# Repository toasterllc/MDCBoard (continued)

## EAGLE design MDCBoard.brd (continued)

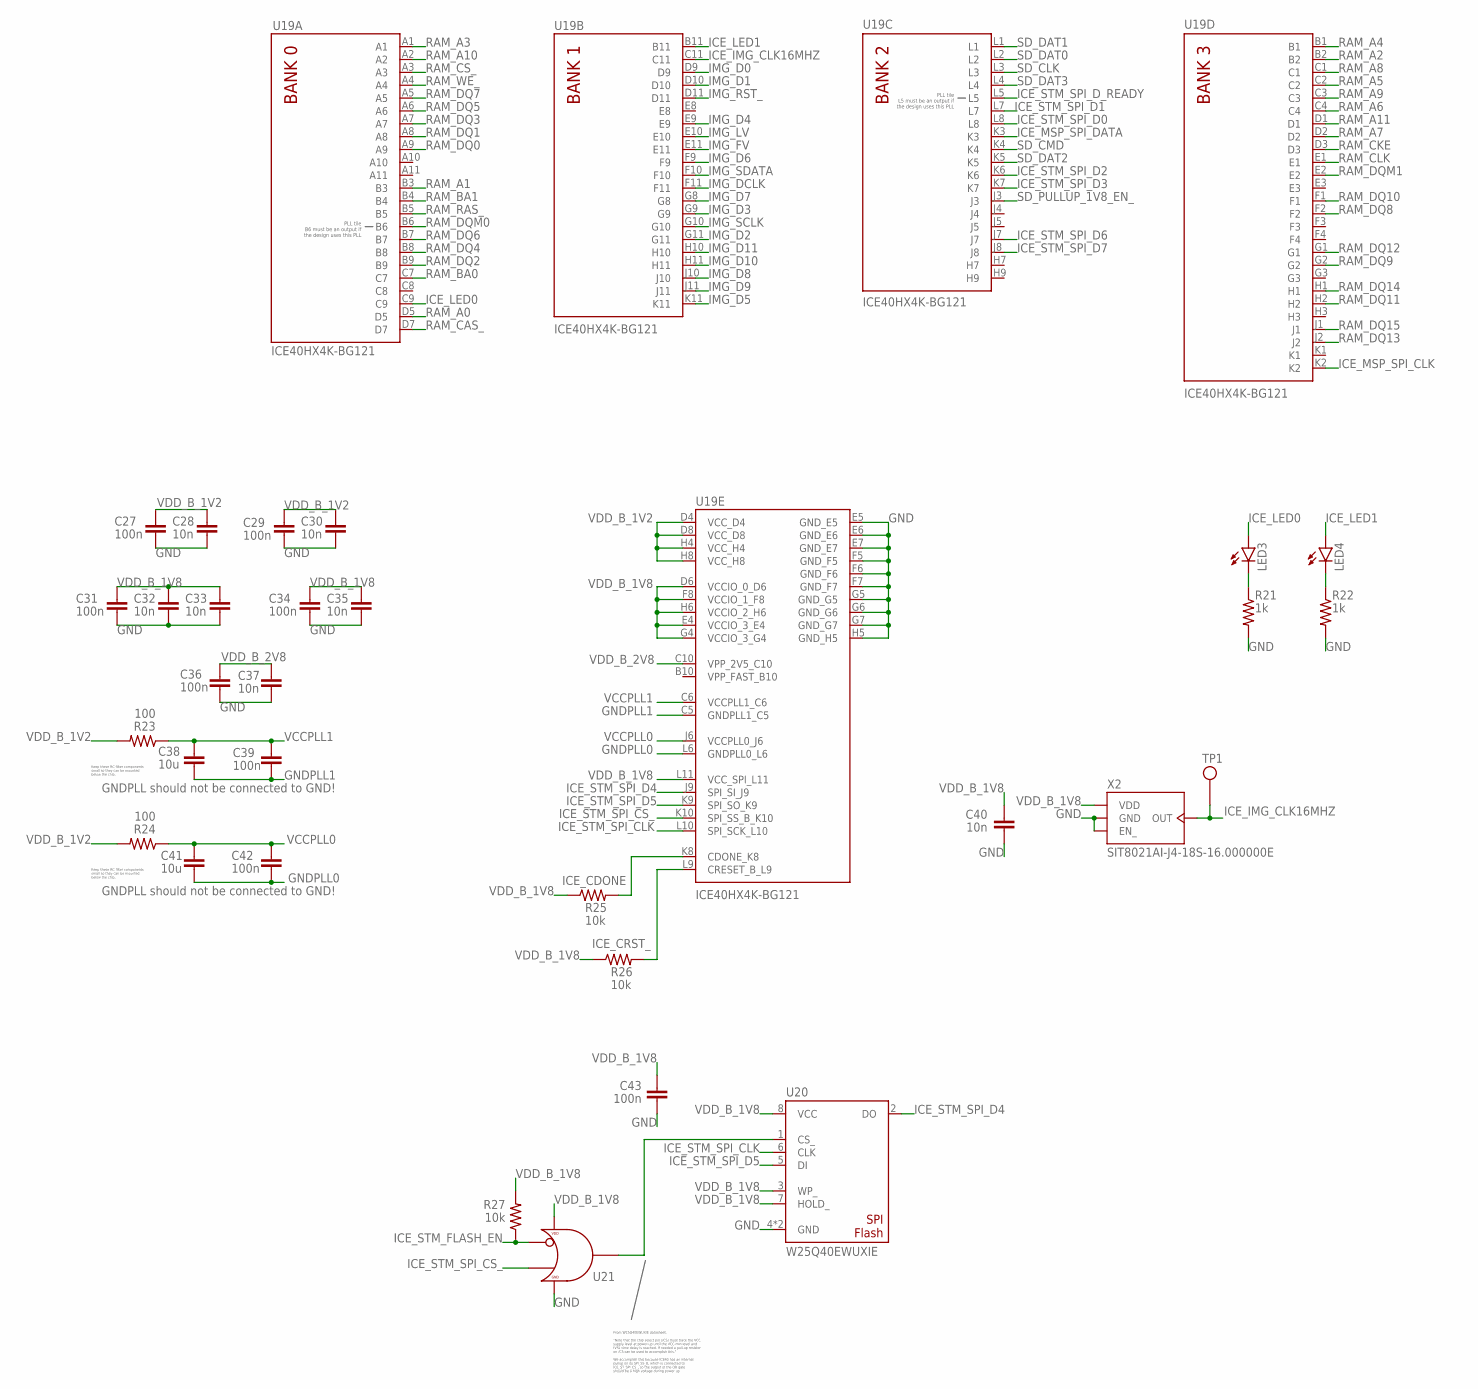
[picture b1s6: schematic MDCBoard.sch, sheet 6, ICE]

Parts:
C27, C29, C31, C34, C36, C39, C42, C43: 100n; 0402
C28, C30, C32, C33, C35, C37, C40: 10n; 0402
C38, C41: 10u; 0805
LED3, LED4: LEDLED-0603; LED-0603
R21, R22: 1k; 0402
R23, R24: 100; 0402
R25, R26, R27: 10k; 0402
TP1: TEST-POINT
U19: LATTICE-ICE40HX4K-BG121
U20: WINBOND-W25Q40EW; WINBOND-W25Q40EWUXIE
U21: NEXPERIA-74LVC1G98-OR-INV-INPUT; NEXPERIA-SOT363
X2: SITIME-SIT8021

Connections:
GND: C27.2, C28.2, C29.2, C30.2, C31.2, C32.2, C33.2, C34.2, C35.2, C36.2, C37.2, C40.2, C43.2, R21.2, R22.2, U19.E5 (GND_E5), U19.E6 (GND_E6), U19.E7 (GND_E7), U19.F5 (GND_F5), U19.F6 (GND_F6), U19.F7 (GND_F7), U19.G5 (GND_G5), U19.G6 (GND_G6), U19.G7 (GND_G7), U19.H5 (GND_H5), U20.4 (GND), U20.9 (GND), U21.2 (GND), U21.3 (GND), X2.1 (EN_), X2.4 (GND); also elsewhere on the board
GNDPLL0: C41.2, C42.2, U19.L6 (GNDPLL0_L6)
GNDPLL1: C38.2, C39.2, U19.C5 (GNDPLL1_C5)
ICE_CDONE: R25.2, U19.K8 (CDONE_K8); also elsewhere on the board
ICE_CRST_: R26.2, U19.L9 (CRESET_B_L9); also elsewhere on the board
ICE_IMG_CLK16MHZ: TP1.X, U19.C11, X2.2 (OUT); also elsewhere on the board
ICE_LED0: LED3.A, U19.C9
ICE_LED1: LED4.A, U19.B11
ICE_MSP_SPI_CLK: U19.K2; also elsewhere on the board
ICE_MSP_SPI_DATA: U19.K3; also elsewhere on the board
ICE_STM_FLASH_EN: R27.1, U21.1 (IN1); also elsewhere on the board
ICE_STM_SPI_CLK: U19.L10 (SPI_SCK_L10), U20.6 (CLK); also elsewhere on the board
ICE_STM_SPI_CS_: U19.K10 (SPI_SS_B_K10), U21.6 (IN2); also elsewhere on the board
ICE_STM_SPI_D0: U19.L8; also elsewhere on the board
ICE_STM_SPI_D1: U19.L7; also elsewhere on the board
ICE_STM_SPI_D2: U19.K6; also elsewhere on the board
ICE_STM_SPI_D3: U19.K7; also elsewhere on the board
ICE_STM_SPI_D4: U19.J9 (SPI_SI_J9), U20.2 (DO); also elsewhere on the board
ICE_STM_SPI_D5: U19.K9 (SPI_SO_K9), U20.5 (DI); also elsewhere on the board
ICE_STM_SPI_D6: U19.J7; also elsewhere on the board
ICE_STM_SPI_D7: U19.J8; also elsewhere on the board
ICE_STM_SPI_D_READY: U19.L5; also elsewhere on the board
IMG_D0: U19.D9; also elsewhere on the board
IMG_D1: U19.D10; also elsewhere on the board
IMG_D2: U19.G11; also elsewhere on the board
IMG_D3: U19.G9; also elsewhere on the board
IMG_D4: U19.E9; also elsewhere on the board
IMG_D5: U19.K11; also elsewhere on the board
IMG_D6: U19.F9; also elsewhere on the board
IMG_D7: U19.G8; also elsewhere on the board
IMG_D8: U19.J10; also elsewhere on the board
IMG_D9: U19.J11; also elsewhere on the board
IMG_D10: U19.H11; also elsewhere on the board
IMG_D11: U19.H10; also elsewhere on the board
IMG_DCLK: U19.F11; also elsewhere on the board
IMG_FV: U19.E11; also elsewhere on the board
IMG_LV: U19.E10; also elsewhere on the board
IMG_RST_: U19.D11; also elsewhere on the board
IMG_SCLK: U19.G10; also elsewhere on the board
IMG_SDATA: U19.F10; also elsewhere on the board
unnamed: LED3.C, R21.1
unnamed: LED4.C, R22.1
unnamed: U20.1 (CS_), U21.4 (OUT)
RAM_A0: U19.D5; also elsewhere on the board
RAM_A1: U19.B3; also elsewhere on the board
RAM_A2: U19.B2; also elsewhere on the board
RAM_A3: U19.A1; also elsewhere on the board
RAM_A4: U19.B1; also elsewhere on the board
RAM_A5: U19.C2; also elsewhere on the board
RAM_A6: U19.C4; also elsewhere on the board
RAM_A7: U19.D2; also elsewhere on the board
RAM_A8: U19.C1; also elsewhere on the board
RAM_A9: U19.C3; also elsewhere on the board
RAM_A10: U19.A2; also elsewhere on the board
RAM_A11: U19.D1; also elsewhere on the board
RAM_BA0: U19.C7; also elsewhere on the board
RAM_BA1: U19.B4; also elsewhere on the board
RAM_CAS_: U19.D7; also elsewhere on the board
RAM_CKE: U19.D3; also elsewhere on the board
RAM_CLK: U19.E1; also elsewhere on the board
RAM_CS_: U19.A3; also elsewhere on the board
RAM_DQ0: U19.A9; also elsewhere on the board
RAM_DQ1: U19.A8; also elsewhere on the board
RAM_DQ2: U19.B9; also elsewhere on the board
RAM_DQ3: U19.A7; also elsewhere on the board
RAM_DQ4: U19.B8; also elsewhere on the board
RAM_DQ5: U19.A6; also elsewhere on the board
RAM_DQ6: U19.B7; also elsewhere on the board
RAM_DQ7: U19.A5; also elsewhere on the board
RAM_DQ8: U19.F2; also elsewhere on the board
RAM_DQ9: U19.G2; also elsewhere on the board
RAM_DQ10: U19.F1; also elsewhere on the board
RAM_DQ11: U19.H2; also elsewhere on the board
RAM_DQ12: U19.G1; also elsewhere on the board
RAM_DQ13: U19.J2; also elsewhere on the board
RAM_DQ14: U19.H1; also elsewhere on the board
RAM_DQ15: U19.J1; also elsewhere on the board
RAM_DQM0: U19.B6; also elsewhere on the board
RAM_DQM1: U19.E2; also elsewhere on the board
RAM_RAS_: U19.B5; also elsewhere on the board
RAM_WE_: U19.A4; also elsewhere on the board
SD_CLK: U19.L3; also elsewhere on the board
SD_CMD: U19.K4; also elsewhere on the board
SD_DAT0: U19.L2; also elsewhere on the board
SD_DAT1: U19.L1; also elsewhere on the board
SD_DAT2: U19.K5; also elsewhere on the board
SD_DAT3: U19.L4; also elsewhere on the board
SD_PULLUP_1V8_EN_: U19.J3; also elsewhere on the board
VCCPLL0: C41.1, C42.1, R24.1, U19.J6 (VCCPLL0_J6)
VCCPLL1: C38.1, C39.1, R23.1, U19.C6 (VCCPLL1_C6)
VDD_B_1V2: C27.1, C28.1, C29.1, C30.1, R23.2, R24.2, U19.D4 (VCC_D4), U19.D8 (VCC_D8), U19.H4 (VCC_H4), U19.H8 (VCC_H8); also elsewhere on the board
VDD_B_1V8: C31.1, C32.1, C33.1, C34.1, C35.1, C40.1, C43.1, R25.1, R26.1, R27.2, U19.D6 (VCCIO_0_D6), U19.E4 (VCCIO_3_E4), U19.F8 (VCCIO_1_F8), U19.G4 (VCCIO_3_G4), U19.H6 (VCCIO_2_H6), U19.L11 (VCC_SPI_L11), U20.3 (WP_), U20.7 (HOLD_), U20.8 (VCC), U21.5 (VDD), X2.3 (VDD); also elsewhere on the board
VDD_B_2V8: C36.1, C37.1, U19.C10 (VPP_2V5_C10); also elsewhere on the board

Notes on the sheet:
GNDPLL should not be connected to GND!
Keep these RC filter components small so they can be mounted below the chip.
From W25Q40EWUXIE datasheet: "Note that the chip select pin (/CS) must track the VCC supply level at power-up until the VCC-min level and tVSL time delay is reached. If needed a pull-up resister on /CS can be used to accomplish this." We accomplish this because ICE40 has an internal pullup on its S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

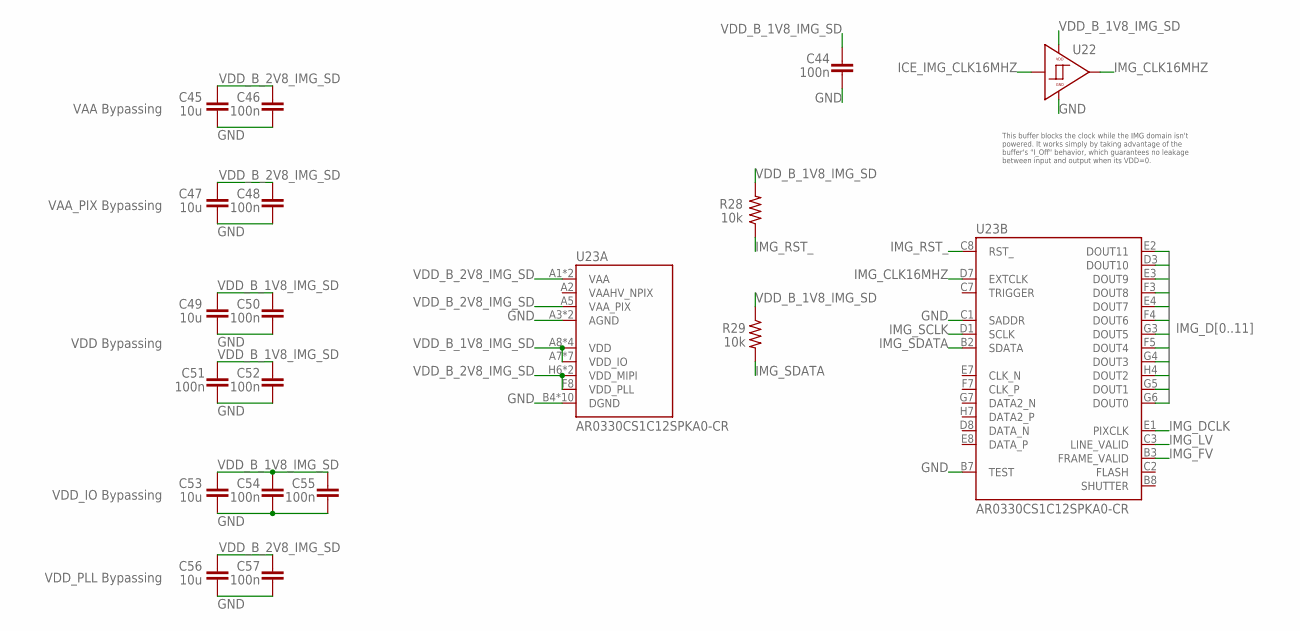
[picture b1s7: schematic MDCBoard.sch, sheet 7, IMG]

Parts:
C44, C46, C48, C50, C51, C52, C54, C55, C57: 100n; 0402
C45, C47, C49, C53, C56: 10u; 0805
R28, R29: 10k; 0402
U22: NEXPERIA-74LVC1G98-BUFFER; NEXPERIA-SOT363
U23: ON-AR0330CS1C12SPKA0

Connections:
GND: C44.2, C45.2, C46.2, C47.2, C48.2, C49.2, C50.2, C51.2, C52.2, C53.2, C54.2, C55.2, C56.2, C57.2, U22.2 (GND), U22.3 (GND), U23.A3 (AGND), U23.B4 (DGND), U23.B5 (AGND), U23.B6 (DGND), U23.B7 (TEST), U23.C1 (SADDR), U23.C4 (DGND), U23.C5 (DGND), U23.C6 (DGND), U23.D4 (DGND), U23.E6 (DGND), U23.G1 (DGND), U23.H2 (DGND), U23.H3 (DGND); also elsewhere on the board
ICE_IMG_CLK16MHZ: U22.6 (IN); also elsewhere on the board
IMG_CLK16MHZ: U22.4 (OUT), U23.D7 (EXTCLK)
IMG_D0: U23.G6 (DOUT0); also elsewhere on the board
IMG_D1: U23.G5 (DOUT1); also elsewhere on the board
IMG_D2: U23.H4 (DOUT2); also elsewhere on the board
IMG_D3: U23.G4 (DOUT3); also elsewhere on the board
IMG_D4: U23.F5 (DOUT4); also elsewhere on the board
IMG_D5: U23.G3 (DOUT5); also elsewhere on the board
IMG_D6: U23.F4 (DOUT6); also elsewhere on the board
IMG_D7: U23.E4 (DOUT7); also elsewhere on the board
IMG_D8: U23.F3 (DOUT8); also elsewhere on the board
IMG_D9: U23.E3 (DOUT9); also elsewhere on the board
IMG_D10: U23.D3 (DOUT10); also elsewhere on the board
IMG_D11: U23.E2 (DOUT11); also elsewhere on the board
IMG_DCLK: U23.E1 (PIXCLK); also elsewhere on the board
IMG_FV: U23.B3 (FRAME_VALID); also elsewhere on the board
IMG_LV: U23.C3 (LINE_VALID); also elsewhere on the board
IMG_RST_: R28.1, U23.C8 (RST_); also elsewhere on the board
IMG_SCLK: U23.D1 (SCLK); also elsewhere on the board
IMG_SDATA: R29.2, U23.B2 (SDATA); also elsewhere on the board
VDD_B_1V8_IMG_SD: C44.1, C49.1, C50.1, C51.1, C52.1, C53.1, C54.1, C55.1, R28.2, R29.1, U22.1 (VDD), U22.5 (VDD), U23.A7 (VDD_IO), U23.A8 (VDD), U23.B1 (VDD), U23.D2 (VDD_IO), U23.D5 (VDD_IO), U23.D6 (VDD_IO), U23.E5 (VDD_IO), U23.F6 (VDD_IO), U23.G2 (VDD), U23.G8 (VDD), U23.H5 (VDD_IO); also elsewhere on the board
VDD_B_2V8_IMG_SD: C45.1, C46.1, C47.1, C48.1, C56.1, C57.1, U23.A1 (VAA), U23.A5 (VAA_PIX), U23.A6 (VAA), U23.F8 (VDD_PLL), U23.H6 (VDD_MIPI), U23.H8 (VDD_MIPI); also elsewhere on the board

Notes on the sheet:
VAA Bypassing
VAA_PIX Bypassing
VDD Bypassing
VDD_IO Bypassing
VDD_PLL Bypassing
This buffer blocks the clock while the IMG domain isn't powered. It works simply by taking advantage of the buffer's "I_Off" behavior, which guarantees no leakage between input and output when its VDD=0.

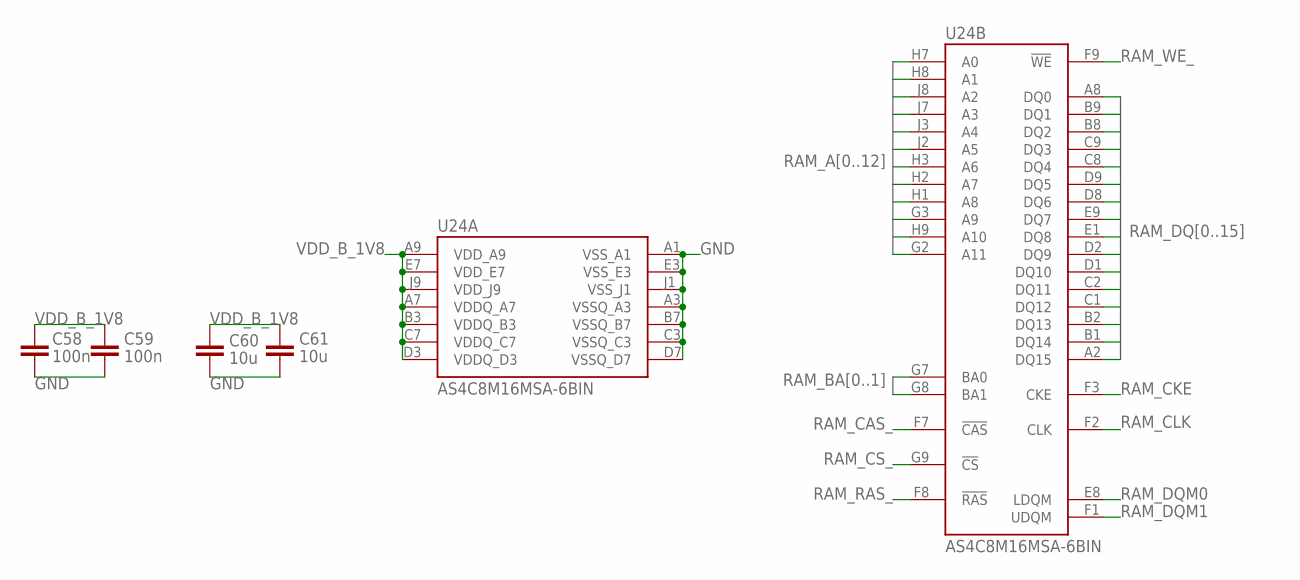
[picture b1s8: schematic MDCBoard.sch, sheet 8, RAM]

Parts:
C58, C59: 100n; 0402
C60, C61: 10u; 0805
U24: ALLIANCE-AS4C8M16MSA-6BIN

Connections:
GND: C58.2, C59.2, C60.2, C61.2, U24.A1 (VSS_A1), U24.A3 (VSSQ_A3), U24.B7 (VSSQ_B7), U24.C3 (VSSQ_C3), U24.D7 (VSSQ_D7), U24.E3 (VSS_E3), U24.J1 (VSS_J1); also elsewhere on the board
RAM_A0: U24.H7 (A0); also elsewhere on the board
RAM_A1: U24.H8 (A1); also elsewhere on the board
RAM_A2: U24.J8 (A2); also elsewhere on the board
RAM_A3: U24.J7 (A3); also elsewhere on the board
RAM_A4: U24.J3 (A4); also elsewhere on the board
RAM_A5: U24.J2 (A5); also elsewhere on the board
RAM_A6: U24.H3 (A6); also elsewhere on the board
RAM_A7: U24.H2 (A7); also elsewhere on the board
RAM_A8: U24.H1 (A8); also elsewhere on the board
RAM_A9: U24.G3 (A9); also elsewhere on the board
RAM_A10: U24.H9 (A10); also elsewhere on the board
RAM_A11: U24.G2 (A11); also elsewhere on the board
RAM_BA0: U24.G7 (BA0); also elsewhere on the board
RAM_BA1: U24.G8 (BA1); also elsewhere on the board
RAM_CAS_: U24.F7 (!CAS!); also elsewhere on the board
RAM_CKE: U24.F3 (CKE); also elsewhere on the board
RAM_CLK: U24.F2 (CLK); also elsewhere on the board
RAM_CS_: U24.G9 (!CS!); also elsewhere on the board
RAM_DQ0: U24.A8 (DQ0); also elsewhere on the board
RAM_DQ1: U24.B9 (DQ1); also elsewhere on the board
RAM_DQ2: U24.B8 (DQ2); also elsewhere on the board
RAM_DQ3: U24.C9 (DQ3); also elsewhere on the board
RAM_DQ4: U24.C8 (DQ4); also elsewhere on the board
RAM_DQ5: U24.D9 (DQ5); also elsewhere on the board
RAM_DQ6: U24.D8 (DQ6); also elsewhere on the board
RAM_DQ7: U24.E9 (DQ7); also elsewhere on the board
RAM_DQ8: U24.E1 (DQ8); also elsewhere on the board
RAM_DQ9: U24.D2 (DQ9); also elsewhere on the board
RAM_DQ10: U24.D1 (DQ10); also elsewhere on the board
RAM_DQ11: U24.C2 (DQ11); also elsewhere on the board
RAM_DQ12: U24.C1 (DQ12); also elsewhere on the board
RAM_DQ13: U24.B2 (DQ13); also elsewhere on the board
RAM_DQ14: U24.B1 (DQ14); also elsewhere on the board
RAM_DQ15: U24.A2 (DQ15); also elsewhere on the board
RAM_DQM0: U24.E8 (LDQM); also elsewhere on the board
RAM_DQM1: U24.F1 (UDQM); also elsewhere on the board
RAM_RAS_: U24.F8 (!RAS!); also elsewhere on the board
RAM_WE_: U24.F9 (!WE!); also elsewhere on the board
VDD_B_1V8: C58.1, C59.1, C60.1, C61.1, U24.A7 (VDDQ_A7), U24.A9 (VDD_A9), U24.B3 (VDDQ_B3), U24.C7 (VDDQ_C7), U24.D3 (VDDQ_D3), U24.E7 (VDD_E7), U24.J9 (VDD_J9); also elsewhere on the board

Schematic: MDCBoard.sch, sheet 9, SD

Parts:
C62: 10u; 0805
C63: 100n; 0402
J9: MICROSD-SOCKET; MOLEX-1051620001
Q5, Q6: DIODESINC-DMG2305UX
R30: 10k; 0402
R31, R32, R33, R34, R35, R36: 20k; 0402
U25: NEXPERIA-74LVC1G98-INVERTER; NEXPERIA-SOT363

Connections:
GND: C62.2, C63.2, J9.GND1 (GND), J9.GND2 (GND), J9.GND3 (GND), J9.GND4 (GND), J9.VSS (GND), U25.2 (GND), U25.3 (GND), U25.6 (GND); also elsewhere on the board
unnamed: Q6.G, U25.4 (OUT)
SD_CLK: J9.CLK, R31.1; also elsewhere on the board
SD_CMD: J9.CMD, R32.1; also elsewhere on the board
SD_DAT0: J9.DAT0, R33.1; also elsewhere on the board
SD_DAT1: J9.DAT1, R34.1; also elsewhere on the board
SD_DAT2: J9.DAT2, R35.1; also elsewhere on the board
SD_DAT3: J9.DAT3, R36.1; also elsewhere on the board
SD_PULLUP: Q5.S, Q6.D, R31.2, R32.2, R33.2, R34.2, R35.2, R36.2
SD_PULLUP_1V8_EN_: Q5.G, R30.1, U25.1 (IN); also elsewhere on the board
VDD_B_1V8_IMG_SD: Q5.D; also elsewhere on the board
VDD_B_2V8_IMG_SD: C62.1, C63.1, J9.VDD, Q6.S, R30.2, U25.5 (VDD); also elsewhere on the board

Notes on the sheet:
Using a 10k pullup (instead of a 100k) to ensure we override ICE40's builtin ~58k pullup which tries to drive this net to 1.8V.
Using 20k pullups so we can hit 400 kHz with open-drain comms: Time to pullup from 0V to 90% of 2.8V: R=20 kΩ C=50 pF t = -R*C*Ln(1-.9) = 2.3 us f = 1/t = 434 kHz
SD Pullup Voltage Switching (2.8V <-> 1.8V)

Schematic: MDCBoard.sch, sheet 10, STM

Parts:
C64: 10n; 0402
C65, C67, C68, C69, C70, C72, C73, C74, C75, C77, C78, C79, C80, C81, C84: 100n; 0402
C66, C71, C76, C82, C83, C85, C86, C87: 2.2u; 0402
H1: TAGCONNECT-TC2030-NL
LED5, LED6: LEDLED-0603; LED-0603
R37, R38: 10k; 0402
R39, R40: 1k; 0402
R41: 3k; 0402
U26: STM-STM32F730; STM-STM32F730I8
X3: SITIME-SIT8021

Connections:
BAT_CHRG_EN_: U26.R11 (PE15_R11); also elsewhere on the board
BAT_CHRG_STAT: U26.R12 (PB10_R12); also elsewhere on the board
GND: C64.2, C65.2, C66.2, C67.2, C68.2, C69.2, C70.2, C71.2, C72.2, C73.2, C74.2, C75.2, C76.2, C77.2, C78.2, C79.2, C80.2, C81.2, C82.2, C83.2, C84.2, C85.2, C86.2, C87.2, H1.3, R39.2, R40.2, R41.1, U26.D5 (VSS_D5), U26.D6 (BOOT0_D6), U26.D7 (VSS_D7), U26.D8 (VSS_D8), U26.D9 (VSS_D9), U26.F2 (VSS_F2), U26.F6 (VSS_F6), U26.F7 (VSS_F7), U26.F8 (VSS_F8), U26.F9 (VSS_F9), U26.F10 (VSS_F10), U26.F12 (VSS_F12), U26.G2 (VSS_G2), U26.G6 (VSS_G6), U26.G7 (VSS_G7), U26.G8 (VSS_G8), U26.G9 (VSS_G9), U26.G10 (VSS_G10), U26.G12 (VSS_G12), U26.H6 (VSS_H6), U26.H7 (VSS_H7), U26.H8 (VSS_H8), U26.H9 (VSS_H9), U26.H10 (VSS_H10), U26.H12 (VSS_H12), U26.J6 (VSS_J6), U26.J7 (VSS_J7), U26.J8 (VSS_J8), U26.J9 (VSS_J9), U26.J10 (VSS_J10), U26.K6 (VSS_K6), U26.K7 (VSS_K7), U26.K8 (VSS_K8), U26.K9 (VSS_K9), U26.K10 (VSS_K10), U26.L4 (BYPASS_REG_L4), U26.M1 (VSSA_M1), U26.M8 (VSS_M8), U26.M9 (VSS_M9), U26.N1 (VREF-_N1), X3.1 (EN_), X3.4 (GND); also elsewhere on the board
ICE_CDONE: U26.R4 (PB1_R4); also elsewhere on the board
ICE_CRST_: U26.R6 (PF11_R6); also elsewhere on the board
ICE_STM_FLASH_EN: U26.K3 (PF5_K3); also elsewhere on the board
ICE_STM_SPI_CLK: U26.M6 (PB2_M6); also elsewhere on the board
ICE_STM_SPI_CS_: U26.R10 (PE12_R10); also elsewhere on the board
ICE_STM_SPI_D0: U26.L3 (PF8_L3); also elsewhere on the board
ICE_STM_SPI_D1: U26.L2 (PF9_L2); also elsewhere on the board
ICE_STM_SPI_D2: U26.K1 (PF7_K1); also elsewhere on the board
ICE_STM_SPI_D3: U26.K2 (PF6_K2); also elsewhere on the board
ICE_STM_SPI_D4: U26.R8 (PE7_R8); also elsewhere on the board
ICE_STM_SPI_D5: U26.P8 (PE8_P8); also elsewhere on the board
ICE_STM_SPI_D6: U26.P9 (PE9_P9); also elsewhere on the board
ICE_STM_SPI_D7: U26.R9 (PE10_R9); also elsewhere on the board
ICE_STM_SPI_D_READY: U26.R2 (PA3_R2); also elsewhere on the board
MSP_RST_: U26.B8 (PG12_B8); also elsewhere on the board
MSP_STM_I2C_SCL: R37.1, U26.A5 (PB8_A5); also elsewhere on the board
MSP_STM_I2C_SDA: R38.1, U26.B4 (PB9_B4); also elsewhere on the board
MSP_TEST: U26.B9 (PG11_B9); also elsewhere on the board
unnamed: C82.1, U26.M10 (VCAP_1_M10)
unnamed: C83.1, U26.F13 (VCAP_2_F13)
unnamed: R41.2, U26.J15 (OTG_HS_REXT_J15)
unnamed: C66.1, U26.J14 (VDD12OTGHS_J14)
unnamed: LED6.C, R40.1
unnamed: LED5.C, R39.1
STM_CLK16MHZ: U26.G1 (PH0_G1), X3.2 (OUT)
STM_LED0: LED6.A, U26.R13 (PB11_R13)
STM_LED1: LED5.A, U26.P13 (PB13_P13)
STM_RST_: C65.1, U26.J1 (NRST_J1)
STM_SWCLK: H1.6, U26.A14 (PA14_A14)
STM_SWDIO: H1.5, U26.A15 (PA13_A15)
USB_D+: U26.R15 (PB15_R15); also elsewhere on the board
USB_D-: U26.R14 (PB14_R14); also elsewhere on the board
VDD_B_1V8_STM: C64.1, C67.1, C68.1, C69.1, C70.1, C71.1, C72.1, C73.1, C74.1, C77.1, C78.1, C79.1, C80.1, C81.1, C86.1, C87.1, U26.C1 (VBAT_C1), U26.C5 (VDD_C5), U26.C6 (PDR_ON_C6), U26.C7 (VDD_C7), U26.C9 (VDD_C9), U26.F3 (VDD_F3), U26.G3 (VDD_G3), U26.G13 (VDD_G13), U26.J12 (VDD_J12), U26.J13 (VDD_J13), U26.K4 (VDD_K4), U26.N8 (VDD_N8), U26.N9 (VDD_N9), U26.N10 (VDD_N10), U26.P1 (VREF+_P1), U26.R1 (VDDA_R1), X3.3 (VDD); also elsewhere on the board
VDD_B_3V3_STM: C75.1, C76.1, C84.1, C85.1, R37.2, R38.2, U26.C8 (VDDSDMMC_C8), U26.H13 (VDDUSB_H13); also elsewhere on the board
VDD_USB_IN: H1.1; also elsewhere on the board

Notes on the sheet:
VDD Bypass Capacitors
VDDA Bypass Capacitors
VDDUSB Bypass Capacitors
≤ 1%
Ceff>1uF @ 3.3V bias
"If no external battery is used in the application, it is recommended to connect the VBAT pin to VDD"
VDDSDMMC Bypass Capacitors

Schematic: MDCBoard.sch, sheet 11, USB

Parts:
FB1: FERRITE-BEAD0402; 0402
J10: USB-C-RECEPTACLE-GSWITCH-7030A; GSWITCH-GT-USB-7030A
R42, R43: 5.1k; 0402
U27: DIODESINC-DT1446-04V-7

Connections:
GND: J10.A12B1 (GND), J10.B12A1 (GND), J10.GND1 (GND), J10.GND2 (GND), J10.GND3 (GND), J10.GND4 (GND), R42.2, R43.2, U27.2 (GND); also elsewhere on the board
unnamed: J10.A5 (CC1), R42.1
unnamed: J10.B5 (CC2), R43.1
unnamed: FB1.1, J10.A9B4 (VBUS), J10.B9A4 (VBUS), U27.4 (IO3), U27.5 (VDD), U27.6 (IO4)
USB_D+: J10.A6 (D+), J10.B6 (D+), U27.3 (IO2); also elsewhere on the board
USB_D-: J10.A7 (D-), J10.B7 (D-), U27.1 (IO1); also elsewhere on the board
VDD_USB_IN: FB1.2; also elsewhere on the board

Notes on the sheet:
Low-pass filter using ferrite bead and bulk capacitance on +VDD net. Based on CurrentSensor design. Ferrite bead specs: - Rated current >> actual current (to prevent bead saturation) - Low DC resistance - Low resonant peaking
5.1k resistor requirements: - Tolerance = 10% (20% is acceptable, but 10% is required if, in the future, we want to sense the source's current capability (by reading the voltage on CC1/CC2), to potentially draw more than 500mA if the source supports it.)

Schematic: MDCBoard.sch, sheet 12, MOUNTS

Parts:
MH1, MH2, MH3: MDC-MOUNT-HOLE
MH4, MH5, MH6: MDC-CUTOUT-HALF

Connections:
GND: MH1.1, MH2.1, MH3.1; also elsewhere on the board

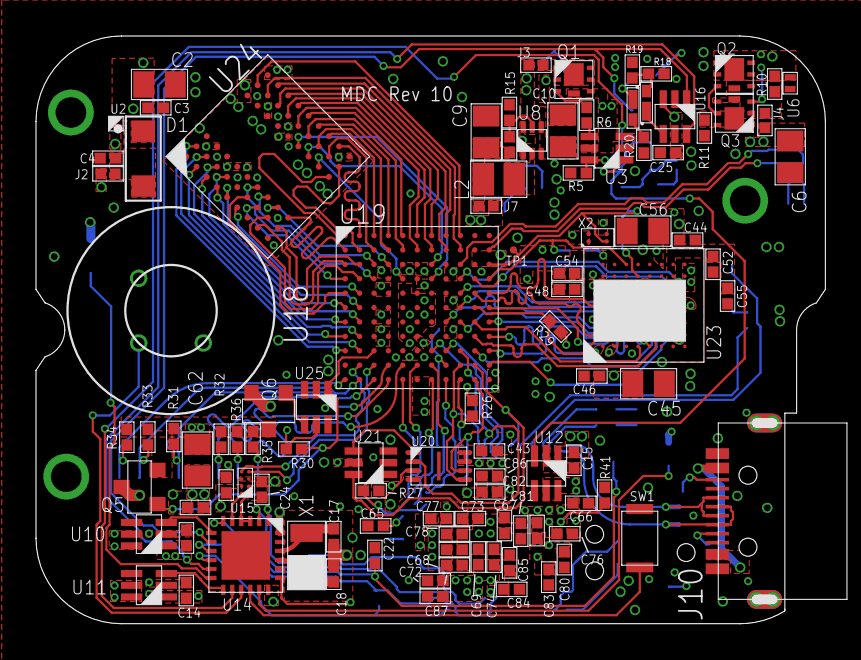
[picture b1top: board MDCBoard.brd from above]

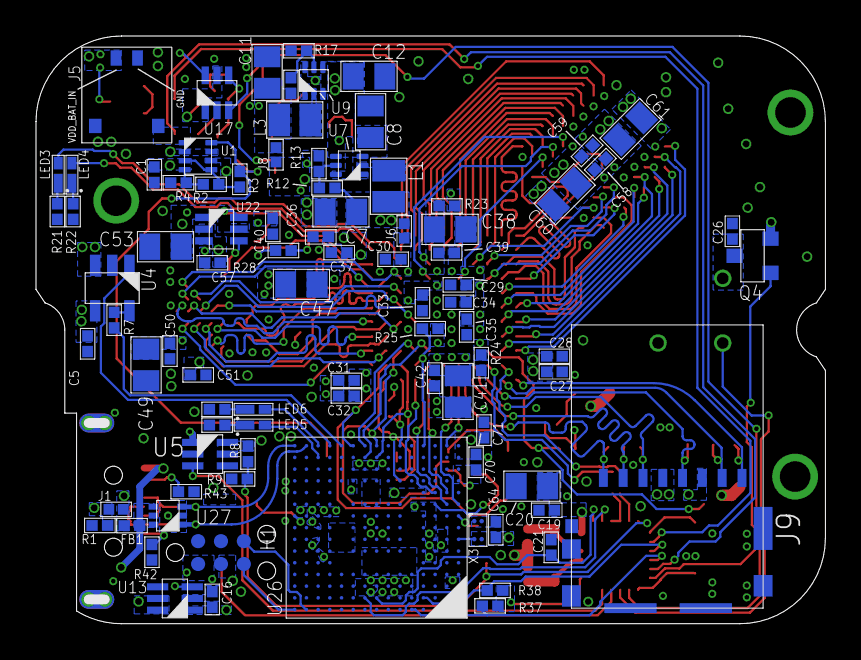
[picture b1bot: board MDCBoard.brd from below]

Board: 4 copper layers, 43.9 x 32.6 mm, 196 parts (90 on the bottom side), 168 nets.

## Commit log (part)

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2022-10-20 Initial commit (add .gitignore)
2022-10-20 Add Rev6 files from MDC repo (board/Rev6 tag)
2022-10-20 Rev6 updates from MDC repo
2022-10-20 Add EagleLibrary submodule
2022-10-20 Rev7 updates:
    - Drive U5 (VDD_BAT voltage buffer) from an STM GPIO instead constantly while connected to USB
    - Battery voltage divider: change resistor values to take advantage of full ADC dynamic range
2022-10-20 Stop using VDD_USB as a signal; use TPS2116DRLR's ST signal instead, pulled to VDD_USB via a 10k resistor
2022-10-20 Swap ICE_STM_SPI nets so that ICERAMWrite can use QSPI to program, while ICEFlashWrite bitbangs
2022-10-20 Add MDCBoard-Rev6 board/schematic for reference while we work on Rev7
2022-10-23 Rev7 progress
2022-10-26 Update comment
2022-10-27 Update STM32 symbol
2022-10-30 Cleanup
2022-10-30 Update EagleLibrary
2022-10-30 Replace NTB0102GF (U16) with TXB0102YZP, because TXB0102YZP is much easier to solder than NTB0102GF.
    NTB0102GF is a very small QFN and it's easy to short the pins together, whereas TXB0102YZP is a BGA.
2022-11-02 Add LEDTest.brd
2022-11-02 Remove LEDTest.brd (use scratch/LEDTest branch)
2022-11-02 Route BAT_CHRG_LVL to MSP430
2022-11-02 Add placeholder for LED flashing circuit (red+green)
2022-11-03 Add power gate to motion sensor, so we can disable it if we don't need to detect motion
2022-11-03 Add separate resistor for both LEDs that MSP430 will control
2022-11-03 Update notes
2022-11-03 Progress
2022-11-03 Update mounting hole size based on enclosure hole size (M1.6 screws, so made diameter 1.7mm)
2022-11-03 Finished rough component placement
2022-11-03 Finished fixing all the keepout DRC errors. 54 airwires to go.
2022-11-03 47 airwires
2022-11-03 44 airwires
2022-11-04 41 airwires
2022-11-04 Commit before moving Q1 subcircuit to be closer to U1
2022-11-04 Done moving Q1 subcircuit to be closer to U1
2022-11-04 36 airwires
2022-11-04 34 airwires
2022-11-04 31 airwires
2022-11-04 30 airwires
2022-11-04 28 airwires
2022-11-04 25 airwires
2022-11-04 22 airwires
2022-11-04 21 airwires
2022-11-04 20 airwires
2022-11-04 17 airwires
2022-11-04 16 airwires
2022-11-04 15 airwires
2022-11-04 14 airwires
2022-11-04 12 airwires
2022-11-04 11 airwires
2022-11-04 10 airwires
2022-11-04 9 airwires
2022-11-04 8 airwires
2022-11-04 7 airwires
2022-11-04 6 airwires
2022-11-04 5 airwires
2022-11-04 4 airwires
2022-11-04 0 airwires
2022-11-04 Make more space around lens mating circle
2022-11-04 Move components further from lens mount ring
2022-11-04 Underway replacing MSP430FR2422 -> MSP430FR2433 so we can have double the FRAM
2022-11-05 Progress replacing MSP430FR2422 -> MSP430FR2433
2022-11-05 0 airwires after replacing MSP430FR2422 -> MSP430FR2433
2022-11-05 Length-matching progress
2022-11-05 Move IMG_D0 to a different ICE40 pad to make the trace a little shorter
2022-11-05 Length-match SD traces
2022-11-05 Add ground vias
2022-11-06 Underway moving motion sensor
2022-11-06 Fixed DRC errors after moving motion sensor
2022-11-09 Replace flashing leds with new osram footprint
2022-11-10 Update LED subcircuit based on testing results
2022-11-10 3 airwires
2022-11-10 2 airwires
2022-11-10 Replace 50Ω resistor with 2x 100Ω resistors
2022-11-10 Preparing to add button
2022-11-10 - Added button - Routed BUTTON_SIGNAL_ to MSP - Updated bypass caps for STM's 3V3 signals
2022-11-10 Reimplemented RAM routing
2022-11-10 Adjust RAM routing
    * RAMClkTraceLen = 12.264 mm
    * ShortestRAMTraceLen = 7.387 mm (-4.877 mm)
    * LongestRAMTraceLen = 18.407 mm (+6.143 mm)
    * Vp [speed of signals in F4-4] = 0.1524 mm / ps
    * f [RAM frequency] = 108 MHz
    * TClkPeriod = 9.26 ns
2022-11-11 Add keepout region for button stopper making contact with button
2022-11-15 Rev5 updates from MDCCode repo (dev/Rev5 branch); corrects part numbers
2022-11-16 Add MDCBoard-Rev5.sch / MDCBoard-Rev5.brd for reference
2022-11-17 Checkout correct version of EagleLibrary for Rev5 board
2022-11-17 Checkout correct version of EagleLibrary for Rev6 board
2022-11-17 Fix VDDA/VREF+ voltages -- apparently they need to be the same voltage as VDD (1.8V), but we increased them to 3.3V. Yikes.
2022-11-17 Add additional STM32 via
2022-11-18 Lower VDD_BAT voltage divider resistance so we get better readings with MSP430 / STM32
2022-11-18 Add part numbers to 100 ohm resistors
2022-11-18 Switch VDD_B MOSFET gate resistor from 10k -> 365k to reduce VDD_BAT droop when enabling VDD_B
2022-11-18 Add part number to button
2022-11-21 Correct size of a single via to be 10mil
2022-11-21 Fix Q3 copper pour for drain net
2022-11-21 Update pad-to-pad clearance to 6mil, per NextPCB spec:
    SMD pad to SMD pad clearance(Pad without hole, different nets): ≥0.15mm
2022-11-21 Fix pad-to-pad clearance DRC errors
2022-11-21 Update pad-to-wire clearance to 6mil, purely to be consistent with the updated pad-to-pad clearance (6mil), and to make our DRC rules more conservative so that our design works with more PCB fabs.
    Fixed ~200 DRC errors that resulted
2022-11-21 Fix more DRC errors from pad-to-wire clearance change
2022-11-21 Update wire-to-via clearance to 6mil, purely to be consistent with the updated pad-to-pad clearance (6mil), and to make our DRC rules more conservative so that our design works with more PCB fabs.
    In the process of fixing resulting DRC errors (~300)
2022-11-21 Fixing clearance DRC errors (139 left)
2022-11-21 Fixing clearance DRC errors (96 left)
2022-11-21 Fixing clearance DRC errors (56 left)
2022-11-21 Fixing clearance DRC errors (5 left)
2022-11-21 Fixed dimension DRC errors
2022-11-21 Update via-to-via clearance to 6mil, purely to be consistent with the updated pad-to-pad clearance (6mil), and to make our DRC rules more conservative so that our design works with more PCB fabs.
    Fixed all resulting DRC errors.
2022-11-21 Length-match SD nets
2022-11-23 Fix GND via nets
2022-11-23 Changed Copper-Dimension DRC distance 15mil -> 16mil
    Fixed dimension DRC errors. Had to move one of the mount points slightly inward, so we'll need to update MDCEnclosure.
2022-11-23 Small adjustment to see if we can fix a NextDFM error
2022-11-24 Expand a polygon to connect several close regions
2022-11-24 Cleanup GND polygons around USB-C receptacle
2022-11-24 Renumber parts
2022-11-24 Cleaning up silkscreen
2022-11-24 Update EagleLibrary (after updating its CAM scripts)
2022-11-24 Update EagleLibrary and DRC rules
2022-11-25 Update part numbers
2022-11-25 Move wires/vias away from tactile switch underside, since it seems like there's exposed metal
    This commit is what we ordered from NextPCB:
    https://www.nextpcb.com/order/orderPacketDetail?group_id=199017&status=production
2022-11-26 Change tactile switch part number to use a part with height=0.6mm (instead of 0.65mm), because 0.6mm is more common
2022-11-30 Update EagleLibrary after fixing 0806 footprint
2022-12-01 Move notes to MDCNotes repo
2022-12-03 Remove STM nets, and prepare for adding MSP<->STM comms
2022-12-03 Remove MSP_HOST_MODE_
2022-12-03 Wired up MSP<->STM I2C comms, and added pullup resistors
2022-12-04 Cleanup board
2022-12-04 Rename LED_FLASH_X_ -> LED_X_
2022-12-04 Switch battery voltage divider dynamic range to [0,3.3]V
    Now uses 1k-3k resistors
2022-12-04 Replace battery connector with Molex 781710002, still need to layout
2022-12-05 Fix DRC errors
2022-12-05 Update part number of other 3k resistor to use the .1% version
2022-12-05 Update resistor tolerance/part numbers. For the battery voltage divider, looks like we can use 0.5% resistors instead of 0.1%, and we'll get <=1.8% error due to the resistors.
2022-12-05 Make solder jumper J1 more accessible so we can solder it easier
2022-12-05 Improve power layer by expanding thin traces
2022-12-05 Add more ground vias
2022-12-05 Cleanup silkscreen
2022-12-05 Update DRC rules to reduce solderpaste size for SMD pads
2022-12-06 I2C updates:
    - Make MSP_STM_I2C_SDA / MSP_STM_I2C_SCL pullups powered by VDD_B_3V3_STM (instead of VDD_A_3V3)
    so that there's zero leakage into STM when STM is unpowered.
    - Wire VDD_B_3V3_STM to an MSP pin so MSP can easily detect STM powering up/down
    - This is necessary because we need initialize I2C when STM powers up, and exit host mode
    and turn off LEDs when STM powers down
    - Ideally the I2C UCCLTOIE ("clock low time-out") interrupt would let us detect STM turning
2022-12-06 Adjust power layer
2022-12-06 Remove errant polygon from ground layer
2022-12-06 This commit is what we ordered from NextPCB:
    https://www.nextpcb.com/order/orderPacketDetail?group_id=201925&status=production
    (There was an earlier Rev7 version that we decided not to assemble, because we realized
    that we want the LEDs to light up when plugging the device in, which required changes.
    Rather than create a Rev8, we're going to pretend the previous Rev7 never happened.)
2022-12-09 Add cream to MOLEX-781710002 pads so the cutouts are generated on a stencil
2022-12-20 Add comment
2022-12-21 Give names to MSP_XIN / MSP_XOUT nets
2023-05-22 Replace LED drivers (Q4 and Q5) with 74LVC1G98GW,125 in the MUX configuration
2023-05-22 Replace U5 with a TPS22919 load switch
2023-05-22 Connect ground of R7 to a 5-V tolerant GPIO of STM32
2023-05-23 Finished with board cutouts, implemented using a circle+triangle on the milling layer
2023-05-23 Update board mount point position
2023-05-23 Update board cutout
2023-05-24 Fixed all DRC errors
2023-05-24 Rename LED nets after removing 4x LEDs
2023-05-24 Add restrict layers for board cutouts. Fix resulting DRC errors.
2023-05-24 Add part number
2023-05-24 Move text
2023-05-24 Replace solder jumpers with JUMPER-SOLDER-CLOSED
2023-05-24 Replace cutouts with MDC-CUTOUT part from library
2023-05-25 Update MDC-CUTOUT part so that dimension layer works properly
2023-06-05 Fix most DRC errors, just dimension errors left which we may not be able to fix
2023-06-05 Replace left board cutout with 2x cutout-half
2023-06-05 Move TagConnect footprint so we can program STM32 without removing the board
2023-06-05 TagConnect footprint progress
2023-06-06 Adjust part labels
2023-06-06 *** This is the commit that we ordered from NextPCB ***
2023-06-08 Progress moving mount point
2023-06-08 Finished moving mount point
2023-06-08 Round mount point position
2023-06-09 Move silkscreen labels
2023-06-09 Add NextPCB-Order directory
2023-06-09 NextPCB-Order progress
2023-06-09 Add PN2 to Q1/Q2/Q3
2023-06-09 NextPCB-Order: filter parts from MDCBoard.mnb / MDCBoard.mnt that NextPCB won't be responsible for mounting
2023-06-10 Update MDC-CUTOUT prefix: X -> MH
2023-06-10 Add assembly attributes to schematic+board devices. Needs some corrections.
2023-06-10 Correct assembly attributes
2023-06-10 AS-MOUNT-NEXTPCB -> AS-MOUNT-FAB
2023-06-10 Update BOM
2023-06-10 Add MDCBoard.csv
2023-06-10 Update NextPCB-Order
2023-06-11 Update part label positions
2023-07-01 Switch TagConnect to 3-post version
2023-07-01 Move right angle in board outline slightly further away from USB-C receptacle, to give a little more clearance between board and receptacle plastic
2023-07-01 Move USB-C receptacle right angle a little more
2023-07-03 Mount LED3,LED4,LED5,LED6 so we can debug board failures more easily
2023-07-03 Update parts AS-MOUNT-FAB / AS-OUR-STOCK
2023-07-03 U15 PN NXB0102UN -> NXB0102UNZ
2023-07-04 Update AS-MOUNT-FAB / AS-OUR-STOCK for: J10, U24, U19, U26
2023-07-04 Update revision text on board: Rev 9 -> Rev 10
2023-07-04 Update board to get rid of airwires
2023-07-04 Update: NextPCB-Order/MDCBoard-Rev10.zip, NextPCB-Order/Centroid.zip
2023-07-04 Update centroid code for NextPCB's expected format
2023-07-04 Add NextPCB-Order/MDCBoard-Centroid.csv.zip
2023-07-05 Add NextPCB-Order/China-Additional-Parts-Needed.numbers
2023-07-08 Add NextPCB-Order/NextPCB-Parts-Stickers.numbers
2023-07-08 Add: NextPCB-Order/Part-Orientation-Symbols.sketch NextPCB-Order/MDCBoard-Solder-Paste-Illustration.sketch
2023-07-08 Add NextPCB-Order/BOM-Part-Orientations.numbers
2023-07-08 Add NextPCB-Order/Diodes-Orientation.sketch
2023-07-08 Update:
    NextPCB-Order/Additional-Parts-Needed.numbers
    NextPCB-Order/BOM-Part-Orientations.numbers
2023-07-13 Add NextPCB-Assembly-Packet.pdf
2023-09-01 Add red/green labels to LED1/LED2 in schematic
2024-07-23 Add LICENSE.md
